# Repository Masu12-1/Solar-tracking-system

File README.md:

# Dual-tracking-solar-system
Dual tracking solar system

## Collaborators
1. Masika - Supervisor

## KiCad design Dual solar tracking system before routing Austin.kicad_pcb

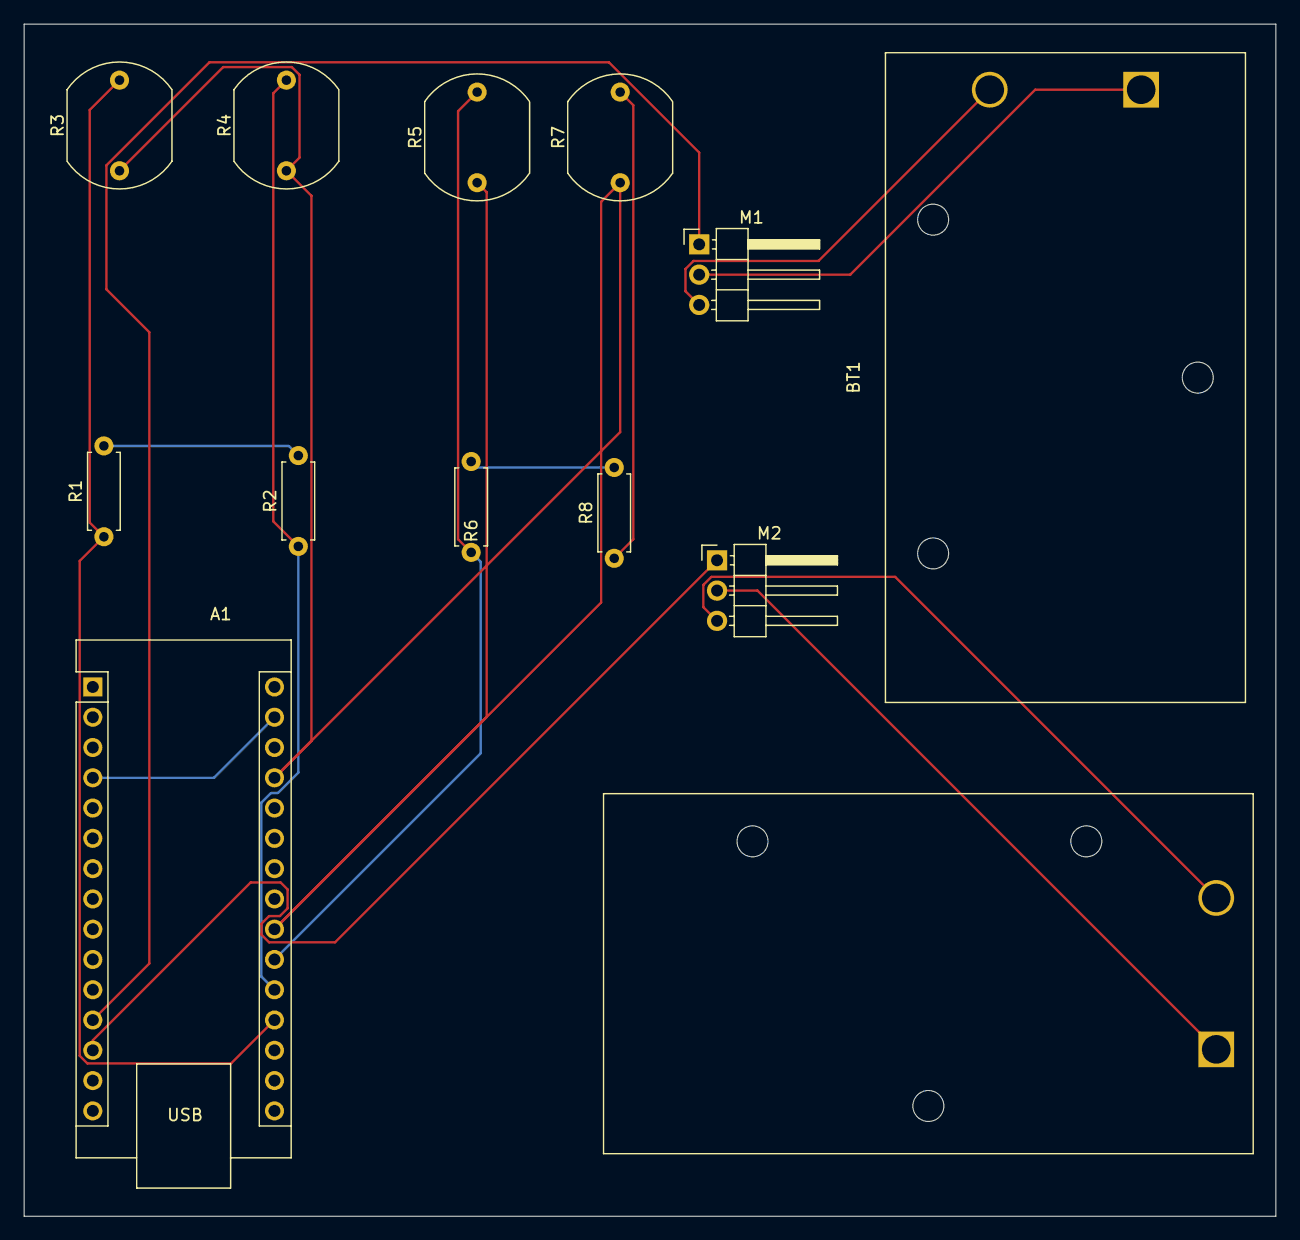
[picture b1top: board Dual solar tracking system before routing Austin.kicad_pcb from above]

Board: 2 copper layers, 105.0 x 100.0 mm, 13 parts (0 on the bottom side), 14 nets.

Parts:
A1: Arduino_Nano_v2.x; Arduino_Nano
BT1: Battery_Cell; BatteryHolder_Eagle_12BH611-GR
BT2: Battery; BatteryHolder_Eagle_12BH611-GR
M1, M2: Motor_Servo; PinHeader_1x03_P2.54mm_Horizontal
R1, R2, R6, R8: R; R_Axial_DIN0207_L6.3mm_D2.5mm_P7.62mm_Horizontal
R3, R4, R5, R7: LDR03; R_LDR_10x8.5mm_P7.6mm_Vertical

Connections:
+5V: A1.22 (A3), A1.27 (+5V), R3.1, R4.1, R5.1, R7.1
unnamed: A1.19 (A0), R1.1, R3.2
unnamed: A1.20 (A1), R2.1, R4.2
unnamed: A1.21 (A2), R5.2, R6.1
unnamed: A1.12 (D9), M1.1 (PWM)
unnamed: A1.13 (D10), M2.1 (PWM)
unnamed: A1.4 (GND), A1.29 (GND)
unnamed: BT1.1 (+), M1.2 (+)
unnamed: BT1.2 (-), M1.3 (-)
unnamed: BT2.1 (+), M2.2 (+)
unnamed: BT2.2 (-), M2.3 (-)
unnamed: R1.2, R2.2
unnamed: R6.2, R8.2
unnamed: R7.2, R8.1
